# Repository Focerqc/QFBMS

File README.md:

# QFBMS — 32s charge-only BMS

QFBMS is a 32-series, charge-only battery-management board for a Fungineers pack. It uses two BQ76952 monitors and an ESP32-C3-MINI-1. The intended software is the VBMS32-target VESC Express firmware plus the supplied VBMS32 Micro package.

The board monitors cells and temperature, measures charging current, controls charging, and balances cells. **Discharge protection is outside the build scope.**

The circuit and routing are incomplete. Firmware compatibility is a design target; the current PCB has not been verified against the supplied software or validated for manufacture.

## Start here

- [Build plan](PLAN.md): the current objective, work order, open decisions, and completion criteria.
- [Design rules](DESIGN_RULES.md): mechanical constraints and how to change the working design.
- [Firmware and package interface](docs/FIRMWARE_INTERFACE.md): behavior and hardware assumptions already defined by the supplied software.

These documents supersede the proposals in [docs/history](docs/history/README.md). The historical discharge-switching instructions and blanket prohibition on moving any component are not the current build plan.

## What stays in place

Keep the placed connectors and bleed resistors R_B1–R_B33 in their existing locations for compatibility with the same case. There is no heatsink. Keep the two BMS monitors in approximately their existing areas; modest local adjustment is acceptable when needed for a sound layout.

Supporting circuitry should follow TI's applicable electrical and layout guidance while fitting these constraints. The existing C_F1–C_F32 back-side placement is a separate unresolved issue; see [Design rules](DESIGN_RULES.md).

## How the software controls the board

The package's LispBM program runs on the ESP32 inside VESC Express. It decides when charging and balancing are allowed. The board-specific C firmware supplies the hardware functions: reading the BQ monitors and commanding balancing over I2C, and controlling external charge-switch circuitry through ESP32 GPIOs.

The supplied package already implements charging voltage, temperature, and current limits, plus balancing rules. Use those definitions as the compatibility baseline. Review the physical circuit, sensing calibration, and startup wiring against them before routing. The BQ automatic-protection configuration alone does not describe the complete charging behavior.

TI supplies the electrical requirements for the monitors and their supporting circuits. A 32s design also needs the stacked-monitor communication and power-domain treatment described in [the reference notes](_reference/ti_bq76952/README.md).

## Open the design

Open `qfbms32.kicad_pro` in KiCad 10. Keep the PCB, schematic, custom footprints in `qfbms.pretty/`, footprint table, and local `3dmodels/` together.

The PCB pad nets are the current working copy. The schematic is incomplete and must be reconciled deliberately; do not overwrite the PCB with an unverified schematic netlist or an old generation script.

The saved [connectivity snapshot](docs/connectivity-snapshot.json) is a migration-era report, not a live status or electrical sign-off. Read the actual board for current connectivity. Dashboard criteria may still reflect older topology assumptions.

## Local tools

From this repository root, install the dashboard dependencies:

```powershell
python -m pip install -r requirements.txt
```

Run each dashboard in its own terminal:

```powershell
python _tools/progress_dashboard/server.py
# http://localhost:5181
```

```powershell
python _tools/pcb_dashboard/server.py
# http://localhost:5180
```

Stop older copies using those ports first. The tools currently expect KiCad 10 at `C:\Program Files\KiCad\10.0`; scripts importing `pcbnew` use KiCad's bundled Python.

## References and history

- [_reference/firmware/](_reference/firmware/): supplied VBMS32 firmware and package source, retained as the compatibility baseline.
- [_reference/ti_bq76952/](_reference/ti_bq76952/README.md): datasheet, evaluation-board material, and links to stacked-monitor guidance.
- [_reference/user_photos/](_reference/user_photos/): placement photographs; IMG_2151 shows the back.
- [Harness drawing](_reference/vfbms32_wiring_32s_best.jpg): external wiring reference; verify its connector pin mapping against the PCB.
- [_reference/pinouts/](_reference/pinouts/): preserved component pinout research.
- [docs/history/](docs/history/README.md): superseded topology, inventory, and finish instructions, retained for traceability.
- [exports/](exports/README.md): regenerated previews and reports, ignored by Git.

The original folder, experiments, and backups remain in the local source repository's migration archive. See [Migration history](docs/MIGRATION.md).

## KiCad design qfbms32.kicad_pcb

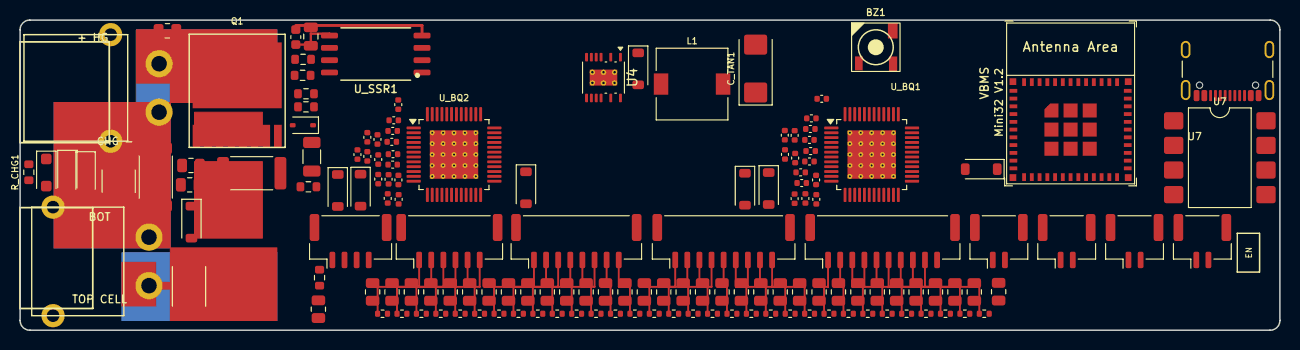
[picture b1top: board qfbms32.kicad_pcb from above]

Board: 2 copper layers, 130.0 x 32.0 mm, 149 parts (0 on the bottom side), 84 nets.

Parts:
BZ1: FUET-5030; Buzzer_5.0x5.0mm_SMD
C_DISC: 10uF; C_1206_3216Metric
C_F1, C_F2, C_F3, C_F4, C_F5, C_F6, C_F7, C_F8, C_F9, C_F10, C_F11, C_F12, C_F13, C_F14, C_F15, C_F16, C_F17, C_F18, C_F19, C_F20, C_F21, C_F22, C_F23, C_F24, C_F25, C_F26, C_F27, C_F28, C_F29, C_F30, C_F31, C_F32: 0.22uF; C_0402_1005Metric
C_FLT1: 10uF_100V; C_1812_4532Metric
C_SSR1: 100nF; C_0603_1608Metric
C_SSR2: 1uF; C_0805_2012Metric
C_TAN1: 100uF_16V; CP_EIA-6032-28_Kemet-C
D_BST1: Schottky; D_SOD-123
D_CHG1, D_CHG2, D_CHG3: DSK320; D_SOD-123F
D_GS1: PDZ16B; D_SOD-323
D_PRI1, D_PRI2, D_PRI3: D_Schottky; D_SOD-123
D_S1: TVS; D_SOD-123
D_SEC1, D_SEC2, D_SEC3: D_Schottky; D_SOD-123
F1: JT 15A; Fuse_2512_6332Metric
FB1: Unmarked; R_0603_1608Metric
J_BAT1: XT30PW-M (BAT); XT30PW-M_Lugs
J_CELL1: 0-8; JST_GH_BM10B-GHS-TBT_1x10-1MP_P1.25mm_Vertical
J_CELL2: 9-16; JST_GH_BM09B-GHS-TBT_1x09-1MP_P1.25mm_Vertical
J_CELL3: 17-24; JST_GH_BM08B-GHS-TBT_1x08-1MP_P1.25mm_Vertical
J_CELL4: 25-32; JST_GH_BM06B-GHS-TBT_1x06-1MP_P1.25mm_Vertical
J_CHG1: XT30PW-F (CHG); XT30PW-F_Lugs
J_COMM1: CAN/5V; JST_GH_BM04B-GHS-TBT_1x04-1MP_P1.25mm_Vertical
J_T1: T1; JST_GH_BM02B-GHS-TBT_1x02-1MP_P1.25mm_Vertical
J_T2: T2; JST_GH_BM02B-GHS-TBT_1x02-1MP_P1.25mm_Vertical
J_T3: T3; JST_GH_BM02B-GHS-TBT_1x02-1MP_P1.25mm_Vertical
J_T4: T4; JST_GH_BM02B-GHS-TBT_1x02-1MP_P1.25mm_Vertical
J_USB1: USB-C; USB_C_Receptacle_16P
L1: 180uH_181; L_7.3x7.3_H4.5
Q1: AGM15T03LL; TOLL-8_AGM15T03LL
R_B1, R_B2, R_B3, R_B4, R_B5, R_B6, R_B7, R_B8, R_B9, R_B10, R_B11, R_B12, R_B13, R_B14, R_B15, R_B16, R_B17, R_B18, R_B19, R_B20, R_B21, R_B22, R_B23, R_B24, R_B25, R_B26, R_B27, R_B28, R_B29, R_B30, R_B31, R_B32, R_B33: 27R0; R_0805_2012Metric
R_CHG1: 100k; R_0603_1608Metric
R_CHG2: 2203; R_0805_2012Metric
R_DSG1: 1000; R_0805_2012Metric
R_F1, R_F2, R_F3, R_F4, R_F5, R_F6, R_F7, R_F8, R_F9, R_F10, R_F11, R_F12, R_F13, R_F14, R_F15, R_F16, R_F17, R_F18, R_F19, R_F20, R_F21, R_F22, R_F23, R_F24, R_F25, R_F26, R_F27, R_F28, R_F29, R_F30, R_F31, R_F32: 20R; R_0402_1005Metric
R_G1: 01X; R_0603_1608Metric
R_GS1: 474; R_0603_1608Metric
R_S1, R_S2: 1000; R_0805_2012Metric
R_SEC1: 01X; R_0603_1608Metric
R_SH1, R_SH2: R001; R_2512_6332Metric
R_SSR1: 01X; R_0603_1608Metric
R_SSR2: 10k; R_0603_1608Metric
U4: LTC7138; Analog_MSOP-12-16-1EP_3x4.039mm_P0.5mm_EP1.651x2.845mm_Ther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
U7: ISO1050 (DUB-8); SMDIP-8_W9.53mm
U_BQ1: BQ7695202 (IC1); TQFP-48-1EP_7x7mm_P0.5mm_EP5x5mm_ThermalVias
U_BQ2: BQ7695202 (IC2); TQFP-48-1EP_7x7mm_P0.5mm_EP5x5mm_ThermalVias
U_ESP1: ESP32-C3-MINI-1
U_SSR1: GSRELAY; H2440_SSR

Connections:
5VExt: J_COMM1.4, U7.8
+3V3: BZ1.1, U7.1
BQ1_VC1: C_F1.1, C_F2.2, R_F32.2, U_BQ1.15
BQ1_VC2: C_F2.1, C_F3.2, R_F31.2, U_BQ1.14
BQ1_VC3: C_F3.1, C_F4.2, R_F30.2, U_BQ1.13
BQ1_VC4: C_F4.1, C_F5.2, R_F29.2, U_BQ1.12
BQ1_VC5: C_F5.1, C_F6.2, R_F28.2, U_BQ1.11
BQ1_VC6: C_F6.1, C_F7.2, R_F27.2, U_BQ1.10
BQ1_VC7: C_F7.1, C_F8.2, R_F26.2, U_BQ1.9
BQ1_VC8: C_F8.1, C_F9.2, R_F25.2, U_BQ1.8
BQ1_VC9: C_F9.1, C_F10.2, R_F24.2, U_BQ1.7
BQ1_VC10: C_F10.1, C_F11.2, R_F23.2, U_BQ1.6
BQ1_VC11: C_F11.1, C_F12.2, R_F22.2, U_BQ1.5
BQ1_VC12: C_F12.1, C_F13.2, R_F21.2, U_BQ1.4
BQ1_VC13: C_F13.1, C_F14.2, R_F20.2, U_BQ1.3
BQ1_VC14: C_F14.1, C_F15.2, R_F19.2, U_BQ1.2
BQ1_VC15: C_F15.1, C_F16.2, R_F18.2, U_BQ1.1
BQ1_VC16: C_F16.1, R_F17.2, U_BQ1.48
BQ2_VC1: C_F17.1, C_F18.2, R_F16.2, U_BQ2.15
BQ2_VC2: C_F18.1, C_F19.2, R_F15.2, U_BQ2.14
BQ2_VC3: C_F19.1, C_F20.2, R_F14.2, U_BQ2.13
BQ2_VC4: C_F20.1, C_F21.2, R_F13.2, U_BQ2.12
BQ2_VC5: C_F21.1, C_F22.2, R_F12.2, U_BQ2.11
BQ2_VC6: C_F22.1, C_F23.2, R_F11.2, U_BQ2.10
BQ2_VC7: C_F23.1, C_F24.2, R_F10.2, U_BQ2.9
BQ2_VC8: C_F24.1, C_F25.2, R_F9.2, U_BQ2.8
BQ2_VC9: C_F25.1, C_F26.2, R_F8.2, U_BQ2.7
BQ2_VC10: C_F26.1, C_F27.2, R_F7.2, U_BQ2.6
BQ2_VC11: C_F27.1, C_F28.2, R_F6.2, U_BQ2.5
BQ2_VC12: C_F28.1, C_F29.2, R_F5.2, U_BQ2.4
BQ2_VC13: C_F29.1, C_F30.2, R_F4.2, U_BQ2.3
BQ2_VC14: C_F30.1, C_F31.2, R_F3.2, U_BQ2.2
BQ2_VC15: C_F31.1, C_F32.2, R_F2.2, U_BQ2.1
BQ2_VC16: C_F32.1, R_F1.2, U_BQ2.48
CANH: J_COMM1.1, U7.7
CANL: J_COMM1.2, U7.6
CELL0: C_F1.2, J_BAT1.2, J_CELL1.10, R_SH1.1, U_BQ1.16
CELL1: J_CELL1.9, R_F32.1
CELL2: J_CELL1.8, R_F31.1
CELL3: J_CELL1.7, R_F30.1
CELL4: J_CELL1.6, R_F29.1
CELL5: J_CELL1.5, R_F28.1
CELL6: J_CELL1.4, R_F27.1
CELL7: J_CELL1.3, R_F26.1
CELL8: J_CELL1.2, R_F25.1
CELL9: J_CELL1.1, R_F24.1
CELL10: J_CELL2.9, R_F23.1
CELL11: J_CELL2.8, R_F22.1
CELL12: J_CELL2.7, R_F21.1
CELL13: J_CELL2.6, R_F20.1
CELL14: J_CELL2.5, R_F19.1
CELL15: J_CELL2.4, R_F18.1
CELL16: C_F17.2, J_CELL2.3, R_F17.1, U_BQ2.16
CELL17: J_CELL2.2, R_F16.1
CELL18: J_CELL2.1, R_F15.1
CELL19: J_CELL3.8, R_F14.1
CELL20: J_CELL3.7, R_F13.1
CELL21: J_CELL3.6, R_F12.1
CELL22: J_CELL3.5, R_F11.1
CELL23: J_CELL3.4, R_F10.1
CELL24: J_CELL3.3, R_F9.1
CELL25: J_CELL3.2, R_F8.1
CELL26: J_CELL3.1, R_F7.1
CELL27: J_CELL4.6, R_F6.1
CELL28: J_CELL4.5, R_F5.1
CELL29: J_CELL4.4, R_F4.1
CELL30: J_CELL4.3, R_F3.1
CELL31: J_CELL4.2, R_F2.1
CELL32: F1.1, J_BAT1.1, J_CELL4.1, R_F1.1, U_SSR1.6
CELL32_FUSED: F1.2, Q1.D
CHG+: D_GS1.2, J_CHG1.1, Q1.2, Q1.3, Q1.4, Q1.5, Q1.6, Q1.7, Q1.8, R_GS1.2
CHG-: J_CHG1.2, R_SH2.2
GND: C_SSR1.2, C_SSR2.2, J_T1.2, J_T2.2, J_T3.2, J_T4.2, R_SSR2.2, U7.4, U_BQ1.17, U_BQ2.17, U_SSR1.4
ISO_GND: J_COMM1.3, U7.5
Q1_GATE: D_GS1.1, Q1.1, R_G1.1, R_GS1.1, R_SSR1.2, R_SSR2.1
SHUNT_MID: R_SH1.2, R_SH2.1
SRN: U_BQ1.20, U_BQ2.20
SRP: U_BQ1.18, U_BQ2.18
SSR_OUT_CHG: R_G1.2, R_SSR1.1
TS1: J_T1.1, U_BQ1.21
TS2: J_T2.1, U_BQ1.22
TS3: J_T3.1, U_BQ1.23
TS4: J_T4.1, U_BQ2.21
VBOOST: C_SSR1.1, C_SSR2.1, U_SSR1.5
